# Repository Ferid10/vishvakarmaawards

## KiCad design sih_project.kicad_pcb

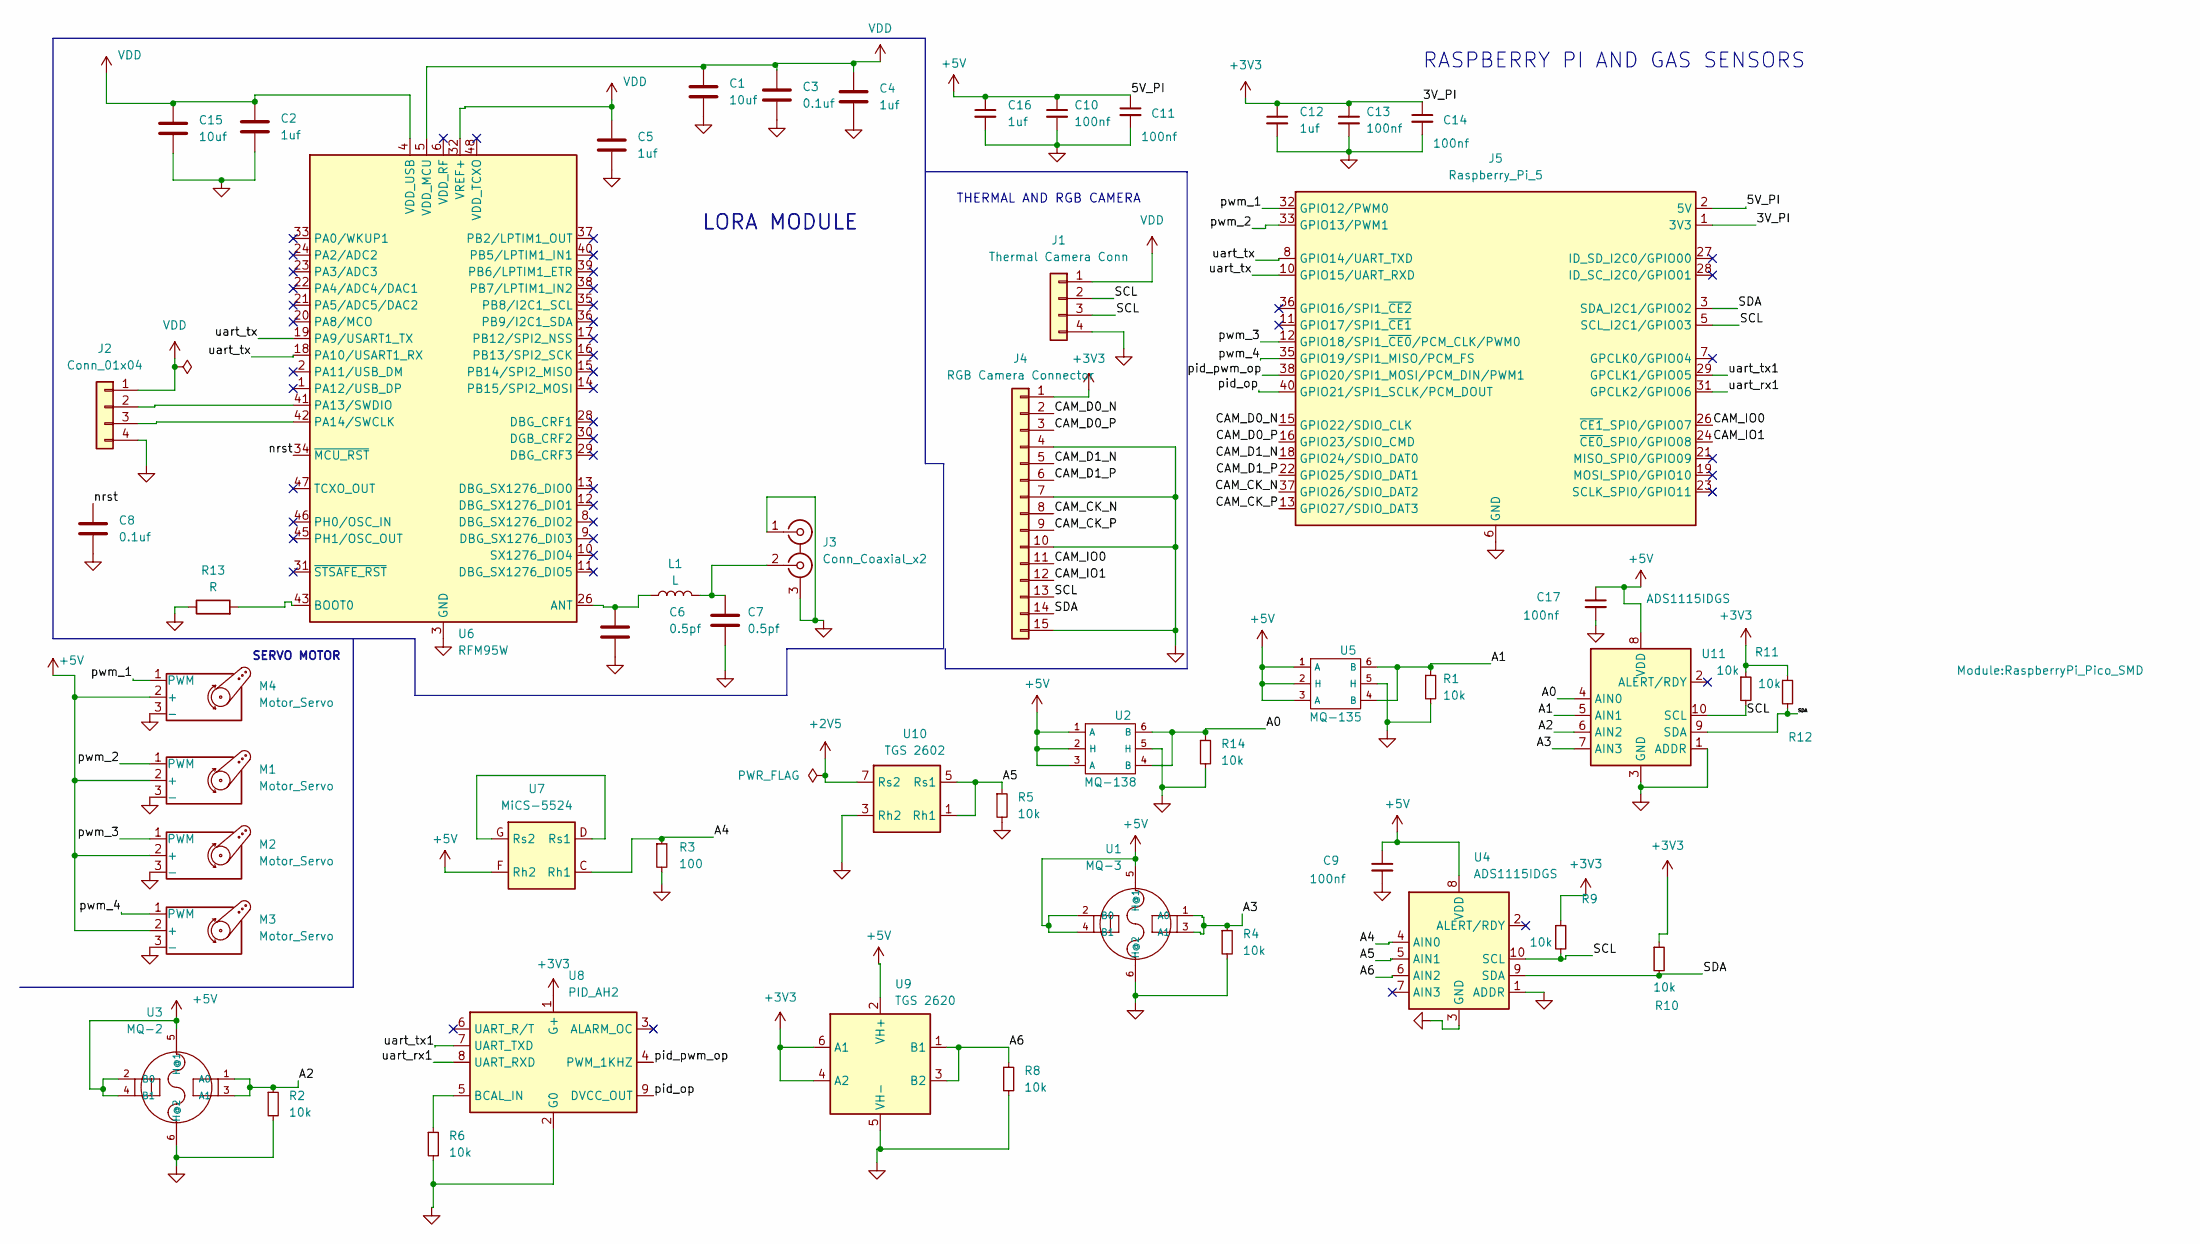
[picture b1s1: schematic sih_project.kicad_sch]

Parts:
C1: 10uf; C_0402_1005Metric
C2, C12: 1uf; C_0603_1608Metric
C3: 0.1uf; C_0402_1005Metric
C4, C5, C16: 1uf; C_0402_1005Metric
C6, C7: 0.5pf; C_0201_0603Metric
C8: 0.1uf; C_0201_0603Metric
C9, C10, C11, C13, C14, C17: 100nf; C_0201_0603Metric
C15: 10uf; C_0603_1608Metric
J1: Thermal Camera Conn; FanPinHeader_1x04_P2.54mm_Vertical
J2: Conn_01x04; FanPinHeader_1x04_P2.54mm_Vertical
J3: Conn_Coaxial_x2; LEMO-EPG.00.302.NLN
J4: RGB Camera Connector; PinHeader_1x15_P1.00mm_Vertical_SMD_Pin1Right
J5: Raspberry_Pi_5; RaspberryPi_Pico_SMD
L1: L; L_0402_1005Metric
M1, M2, M3, M4: Motor_Servo; PinHeader_1x03_P2.54mm_Horizontal
R1, R2, R4, R5, R6, R8, R9, R10, R11, R12, R14: 10k; R_0603_1608Metric
R3: 100; R_0603_1608Metric
R13: R; R_0402_1005Metric
U1: MQ-3; MQ-6; MPN MQ-2
U2: MQ-138; ST_HLGA-6_3.76x4.72mm_P1.65mm
U3: MQ-2; MQ-6; MPN MQ-2
U4, U11: ADS1115IDGS; TSSOP-10_3x3mm_P0.5mm
U5: MQ-135; InvenSense_ICS-43434-6_3.5x2.65mm
U6: RFM95W; CMWX1ZZABZ
U7: MiCS-5524; Sensortech_MiCS_5x7mm_P1.25mm
U8: PID_AH2; Senseair_S8_Up
U9: TGS 2620; MQ-6
U10: TGS 2602; Winson_GM-402B_5x5mm_P1.27mm

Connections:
+2V5: U10.7 (Rs2)
+3V3: C12.1, C13.1, C14.1, J4.1, J5.1 (3V3), J5.17 (3V3), R9.1, R10.1, R11.1, R12.1, U8.1 (G+), U9.4 (A2), U9.6 (A1)
+5V: C9.1, C10.1, C11.1, C16.1, C17.1, J5.2 (5V), J5.4 (5V), M1.2 (+), M2.2 (+), M3.2 (+), M4.2 (+), U1.2 (B0), U1.4 (B1), U1.5 (H@1), U2.1 (A), U2.2 (H), U2.3 (A), U3.2 (B0), U3.4 (B1), U3.5 (H@1), U4.8 (VDD), U5.1 (A), U5.2 (H), U5.3 (A), U7.F (Rh2), U9.2 (VH+), U11.8 (VDD)
/A0: R14.1, U2.4 (B), U2.6 (B), U11.4 (AIN0)
/A1: R1.1, U5.4 (B), U5.6 (B), U11.5 (AIN1)
/A2: R2.1, U3.1 (A0), U3.3 (A1), U11.6 (AIN2)
/A3: R4.1, U1.1 (A0), U1.3 (A1), U11.7 (AIN3)
/A4: R3.1, U4.4 (AIN0), U7.C (Rh1)
/A5: R5.1, U4.5 (AIN1), U10.1 (Rh1), U10.5 (Rs1)
/A6: R8.1, U4.6 (AIN2), U9.1 (B1), U9.3 (B2)
/CAM_CK_N: J4.8, J5.37 (GPIO26/SDIO_DAT2)
/CAM_CK_P: J4.9, J5.13 (GPIO27/SDIO_DAT3)
/CAM_D0_N: J4.2, J5.15 (GPIO22/SDIO_CLK)
/CAM_D0_P: J4.3, J5.16 (GPIO23/SDIO_CMD)
/CAM_D1_N: J4.5, J5.18 (GPIO24/SDIO_DAT0)
/CAM_D1_P: J4.6, J5.22 (GPIO25/SDIO_DAT1)
/CAM_IO0: J4.11, J5.26 (~CE1_SPI0/GPIO07)
/CAM_IO1: J4.12, J5.24 (~CE0_SPI0/GPIO08)
/SCL: J1.2, J1.3, J4.13, J5.5 (SCL_I2C1/GPIO03), R9.2, R11.2, U4.10 (SCL), U11.10 (SCL)
/SDA: J4.14, J5.3 (SDA_I2C1/GPIO02), R10.2, R12.2, U4.9 (SDA), U11.9 (SDA)
/nrst: C8.1, U6.34 (~MCU_RST)
/pid_op: J5.40 (GPIO21/SPI1_SCLK/PCM_DOUT), U8.9 (DVCC_OUT)
/pid_pwm_op: J5.38 (GPIO20/SPI1_MOSI/PCM_DIN/PWM1), U8.4 (PWM_1KHZ)
/pwm_1: J5.32 (GPIO12/PWM0), M4.1 (PWM)
/pwm_2: J5.33 (GPIO13/PWM1), M1.1 (PWM)
/pwm_3: J5.12 (GPIO18/SPI1_~CE0/PCM_CLK/PWM0), M2.1 (PWM)
/pwm_4: J5.35 (GPIO19/SPI1_MISO/PCM_FS), M3.1 (PWM)
/uart_rx1: J5.31 (GPCLK2/GPIO06), U8.8 (UART_RXD)
/uart_tx: J5.8 (GPIO14/UART_TXD), J5.10 (GPIO15/UART_RXD), U6.18 (PA10/USART1_RX), U6.19 (PA9/USART1_TX)
/uart_tx1: J5.29 (GPCLK1/GPIO05), U8.7 (UART_TXD)
GND: C1.2, C2.2, C3.2, C4.2, C5.2, C6.2, C7.2, C8.2, C9.2, C10.2, C11.2, C12.2, C13.2, C14.2, C15.2, C16.2, C17.2, J1.4, J2.4, J3.1 (IN1), J3.3 (EXT), J4.4, J4.7, J4.10, J4.15, J5.6 (GND), J5.9 (GND), J5.14 (GND), J5.20 (GND), J5.25 (GND), J5.30 (GND), J5.34 (GND), J5.39 (GND), M1.3 (-), M2.3 (-), M3.3 (-), M4.3 (-), R1.2, R2.2, R3.2, R4.2, R5.2, R6.2, R8.2, R13.1, R14.2, U1.6 (H@2), U2.5 (H), U3.6 (H@2), U4.1 (ADDR), U4.3 (GND), U5.5 (H), U6.3 (GND), U6.7 (GND), U6.25 (GND), U6.27 (GND), U6.44 (GND), U6.49 (GND), U6.50 (GND), U6.51 (GND), U6.52 (GND), U6.53 (GND), U6.54 (GND), U6.55 (GND), U6.56 (GND), U6.57 (GND), U8.2 (G0), U9.5 (VH-), U10.3 (Rh2), U11.1 (ADDR), U11.3 (GND)
unnamed: J2.2, U6.41 (PA13/SWDIO)
unnamed: J2.3, U6.42 (PA14/SWCLK)
unnamed: C7.1, J3.2 (IN2), L1.2
unnamed: C6.1, L1.1, U6.26 (ANT)
unnamed: R13.2, U6.43 (BOOT0)
unnamed: U7.D (Rs1), U7.G (Rs2)
unnamed: R6.1, U8.5 (BCAL_IN)
VDD: C1.1, C2.1, C3.1, C4.1, C5.1, C15.1, J1.1, J2.1, U6.4 (VDD_USB), U6.5 (VDD_MCU), U6.32 (VREF+)

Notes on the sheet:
THERMAL AND RGB CAMERA
LORA MODULE
SERVO MOTOR
RASPBERRY PI AND GAS SENSORS

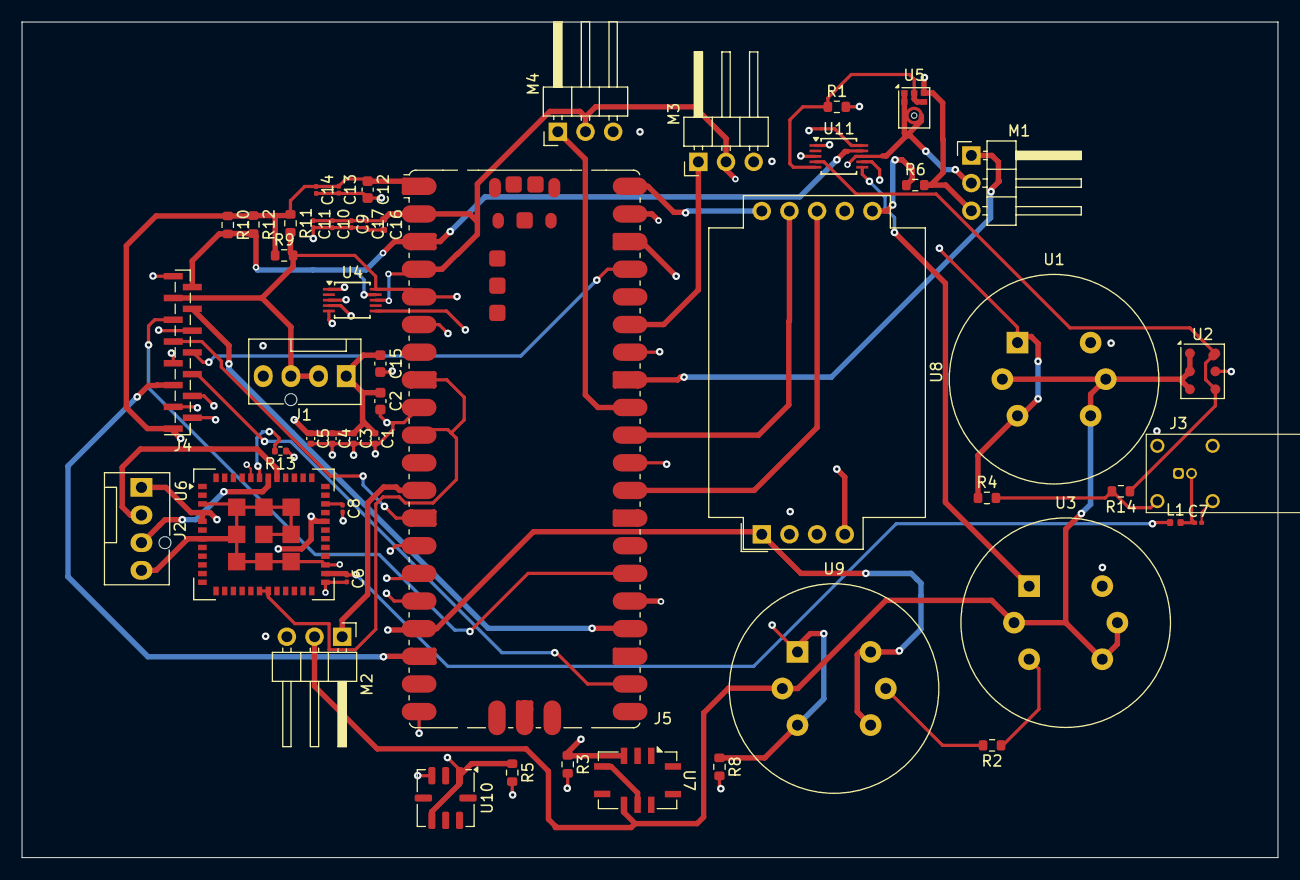
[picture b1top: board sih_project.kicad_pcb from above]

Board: 4 copper layers, 115.4 x 76.8 mm, 51 parts (0 on the bottom side), 38 nets.
